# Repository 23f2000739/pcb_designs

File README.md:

# pcb_designs
* ⚙️ **[Buck Converter design](./buck_converter/)**
* ⚙️ **[Regulated Power Supply design](./power_supply/)**

 ## projects by--
 -Shreyasee Routray

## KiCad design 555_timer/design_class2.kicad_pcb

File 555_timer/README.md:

# LM555 Astable Multivibrator 

A free-running oscillator built around the LM555N timer, designed in KiCad.
It blinks an LED at about 1 Hz from a 9V supply.

## Overview
The LM555 is wired in astable mode. The timing capacitor charges through
R1 and R3 and discharges through R3 into the discharge pin, so the output
switches between HIGH and LOW on its own with no external trigger. The
output drives an LED through a current-limiting resistor.

## Circuit description
- **U1 (LM555N):** timer IC in astable mode
- **R1, R3, C2:** timing network
- **C1:** 0.01 µF decoupling capacitor on the control-voltage pin (pin 5)
- **R2 + D1:** LED output indicator with current-limiting resistor
- Pins 2 (TRIG) and 6 (THRES) are tied together and connected to C2
- Reset pin (4) is tied to Vcc, so the timer is always enabled

## Component values
| Ref | Value | Function |
|---|---|---|
| U1 | LM555N | Timer IC |
| R1 | 3.9 kΩ | Timing resistor |
| R3 | 68 kΩ | Timing resistor |
| C2 | 10 µF / 16 V (electrolytic) | Timing capacitor |
| C1 | 0.01 µF | Control-pin decoupling |
| R2 | 1 kΩ | LED current limiter |
| D1 | LED | Output indicator |

## Working principle
1. C2 charges through R1 and R3 toward Vcc.
2. At 2/3 Vcc the output goes LOW and C2 discharges through R3.
3. At 1/3 Vcc the output goes HIGH and C2 charges again.
4. This repeats continuously, so the LED blinks.

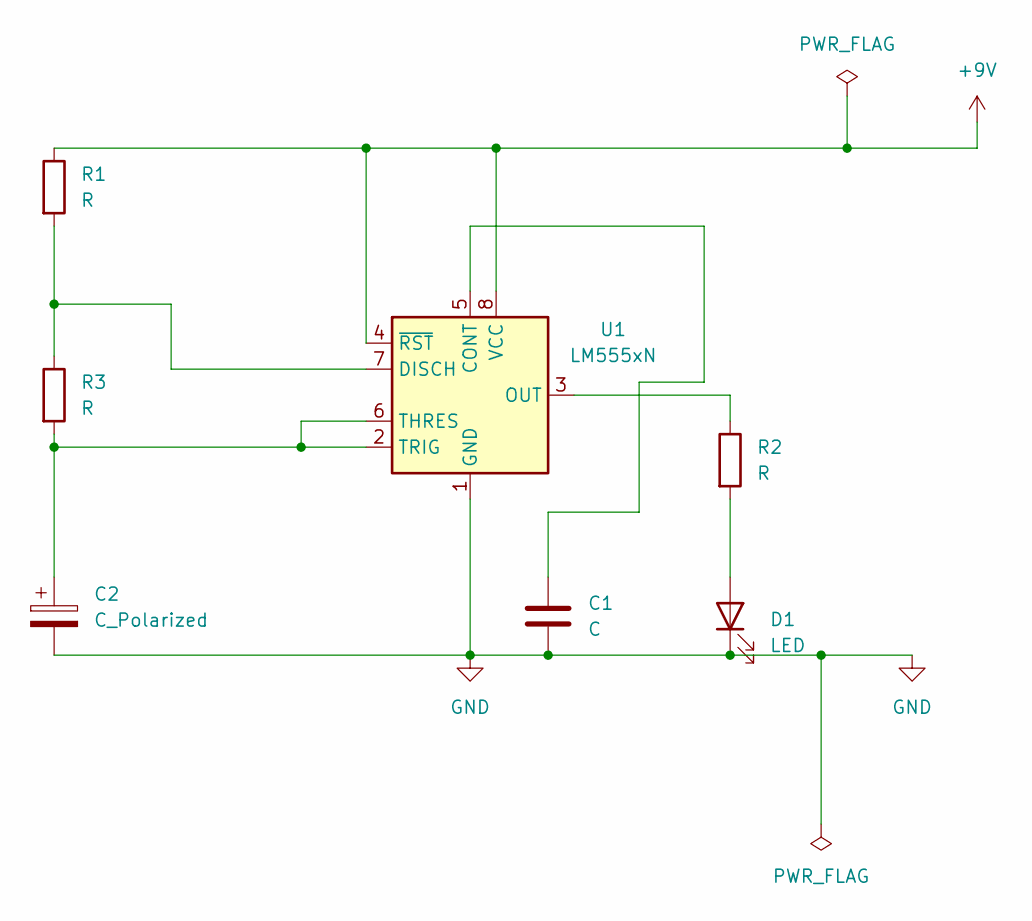
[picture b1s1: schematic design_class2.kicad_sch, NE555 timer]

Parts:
C1: C; C_Disc_D5.0mm_W2.5mm_P2.50mm
C2: C_Polarized; CP_Radial_D5.0mm_P2.00mm
D1: LED; LED_D5.0mm
R1, R2, R3: R; R_Axial_DIN0207_L6.3mm_D2.5mm_P7.62mm_Horizontal
U1: LM555xN; DIP-8_W7.62mm

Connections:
+9V: R1.1, U1.4 (~RST), U1.8 (VCC)
GND: C1.2, C2.2, D1.1 (K), U1.1 (GND)
unnamed: D1.2 (A), R2.2
unnamed: C1.1, U1.5 (CONT)
unnamed: R1.2, R3.1, U1.7 (DISCH)
unnamed: R2.1, U1.3 (OUT)
unnamed: C2.1, R3.2, U1.2 (TRIG), U1.6 (THRES)

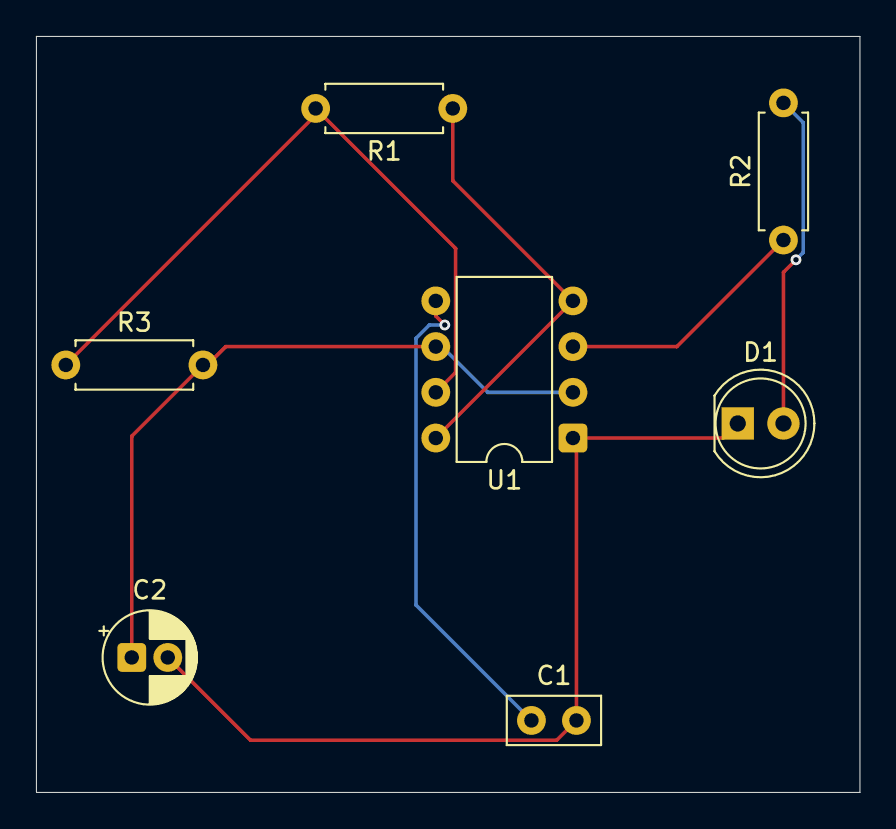
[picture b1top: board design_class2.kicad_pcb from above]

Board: 2 copper layers, 45.8 x 42.0 mm, 7 parts (0 on the bottom side), 7 nets.

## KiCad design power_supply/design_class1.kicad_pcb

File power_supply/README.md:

# 5V Regulated Power Supply (LM7805)

A linear regulated 5V DC power supply designed in KiCad. It converts an AC
transformer output into a stable 5V DC output using a bridge rectifier,
a reservoir capacitor and an LM7805 voltage regulator.

## Overview
The AC input is full-wave rectified by a bridge of four 1N4007 diodes and
smoothed by a filter capacitor. The LM7805 then regulates the DC voltage
down to a fixed 5V. A power LED shows when the output is live.

## Specifications
- Input: 9V-12V AC (from a step-down transformer)
- Output: 5V DC regulated
- Maximum output current: 1A (heatsink recommended at higher loads)
- Regulator: LM7805, TO-220 package

## Circuit description
- **J1:** AC input connector
- **D1-D4 (1N4007):** full-wave bridge rectifier
- **C1:** polarized filter (reservoir) capacitor
- **C2, C3:** high-frequency decoupling capacitors at the regulator input and output
- **U1 (LM7805):** 5V linear voltage regulator
- **R1 + D5:** power indicator LED with current-limiting resistor

## Working principle
1. The transformer steps the mains voltage down to a low AC voltage.
2. The bridge rectifier converts AC to pulsating DC.
3. C1 smooths the pulsating DC into DC with small ripple.
4. The LM7805 regulates this to a constant 5V.
5. C3 stabilizes the output, and the LED indicates power.

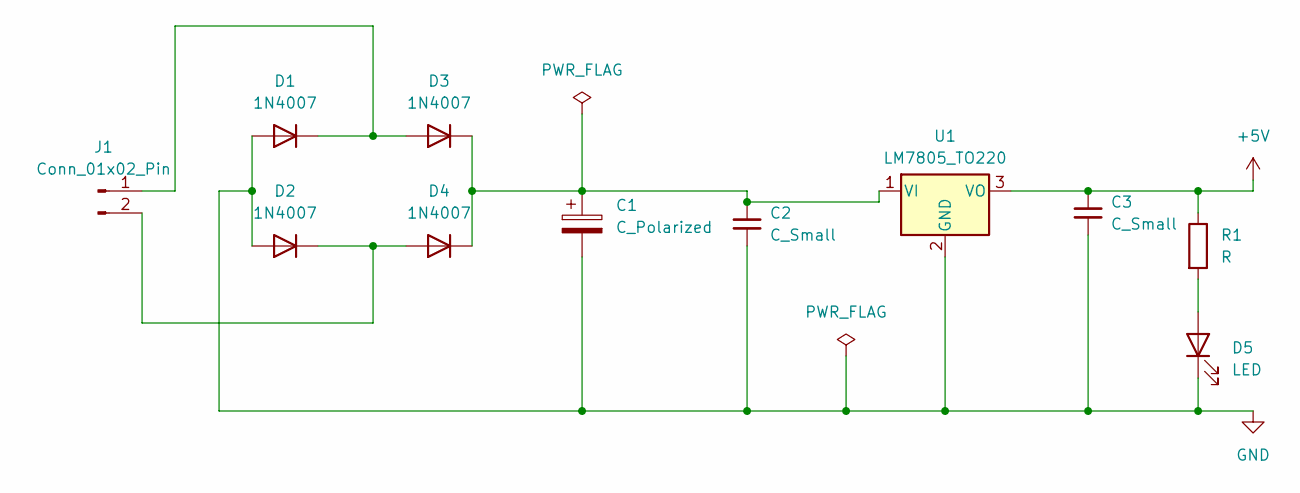
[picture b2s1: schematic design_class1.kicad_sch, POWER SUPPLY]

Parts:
C1: C_Polarized; C_0201_0603Metric
C2, C3: C_Small; C_0402_1005Metric_Pad0.74x0.62mm_HandSolder
D1, D2, D3, D4: 1N4007; D_DO-15_P10.16mm_Horizontal
D5: LED; LED_0201_0603Metric
J1: Conn_01x02_Pin; PinHeader_1x02_P1.00mm_Vertical
R1: R; R_0201_0603Metric
U1: LM7805_TO220; TO-220-3_Vertical

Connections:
+5V: C3.1, R1.1, U1.3 (VO)
GND: C1.2, C2.2, C3.2, D1.2 (A), D2.2 (A), D5.1 (K), U1.2 (GND)
unnamed: D1.1 (K), D3.2 (A), J1.1
unnamed: D2.1 (K), D4.2 (A), J1.2
unnamed: C1.1, C2.1, D3.1 (K), D4.1 (K), U1.1 (VI)
unnamed: D5.2 (A), R1.2

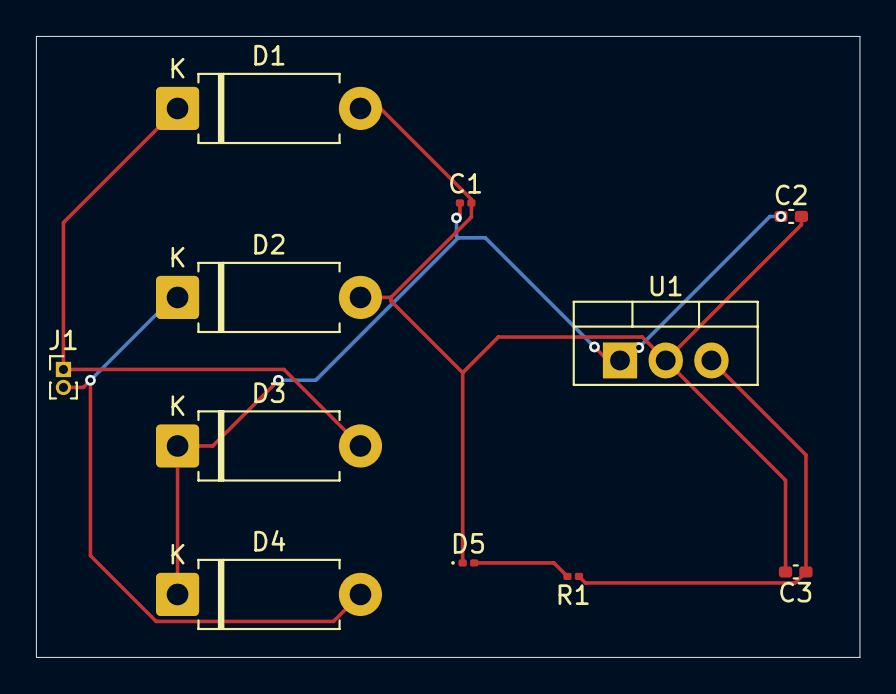
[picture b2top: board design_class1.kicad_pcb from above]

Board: 2 copper layers, 45.8 x 34.5 mm, 11 parts (0 on the bottom side), 6 nets.

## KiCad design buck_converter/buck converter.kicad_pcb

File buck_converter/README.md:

# LM2596 5V Buck Converter

A 5V fixed-output step-down (buck) DC-DC converter, designed in KiCad
(schematic capture and 2-layer PCB layout).

## Overview
The board steps a higher DC input voltage down to a regulated 5V using the
LM2596S-5 switching regulator (150 kHz, up to 3A). 

## Specifications
- Input voltage: 7V to 24V DC (limited by the 35V input capacitor rating)
- Output voltage: 5V fixed
- Maximum output current: up to 3A (with adequate heat dissipation)
- Switching frequency: 150 kHz (typical)
- Board: 2-layer PCB, through-hole connectors, SMD regulator/diode/inductor

- ## Circuit description
- **U1 – LM2596S-5:** integrated switch and control circuit; feedback pin
  connected directly to the 5V output (fixed-voltage version)
- **C1 – 100µF/35V:** input capacitor
- **L1:** energy-storage inductor
- **D2 – 1N5822:** Schottky catch diode
- **C2 – 330µF/10V:** output filter capacitor
- **D1 + R1 (330Ω):** power indicator LED
- **J1 / J2:** input and output connectors
- ON/OFF pin tied to GND, so the regulator is always enabled

- ## PCB design notes
- 1.2mm traces for input and output paths
- Catch diode and capacitors placed close to the regulator to keep the
  switching loop short.

- 

## 3d view

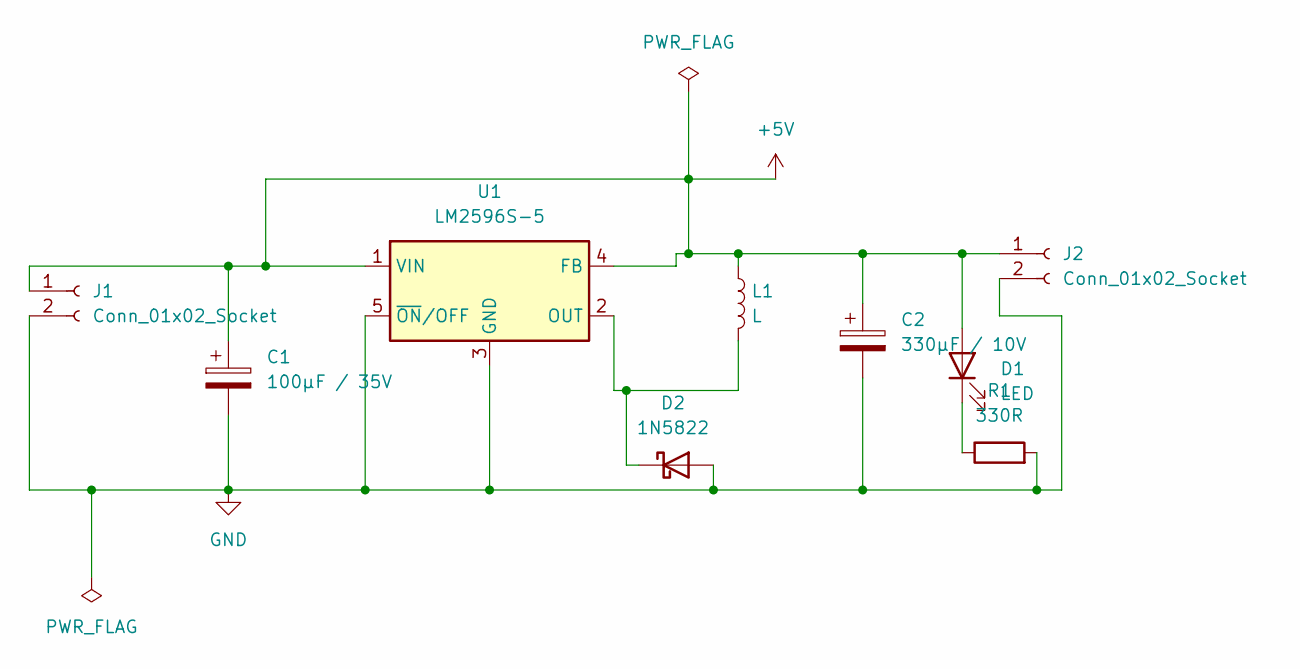
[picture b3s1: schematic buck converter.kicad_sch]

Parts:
C1: 100µF / 35V; CP_Radial_D6.3mm_P2.50mm
C2: 330µF / 10V; CP_Radial_D6.3mm_P2.50mm
D1: LED; LED_0805_2012Metric
D2: 1N5822; D_SMA
J1, J2: Conn_01x02_Socket; PinHeader_1x02_P2.54mm_Vertical
L1: L; L_7.3x7.3_H4.5
R1: 330R; R_0805_2012Metric
U1: LM2596S-5; TO-263-5_TabPin3

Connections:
+5V: C1.1, C2.1, D1.2 (A), J1.1, J2.1, L1.1, U1.1 (VIN), U1.4 (FB)
GND: C1.2, C2.2, D2.2 (A), J1.2, J2.2, R1.2, U1.3 (GND), U1.5 (~ON/OFF)
unnamed: D1.1 (K), R1.1
unnamed: D2.1 (K), L1.2, U1.2 (OUT)

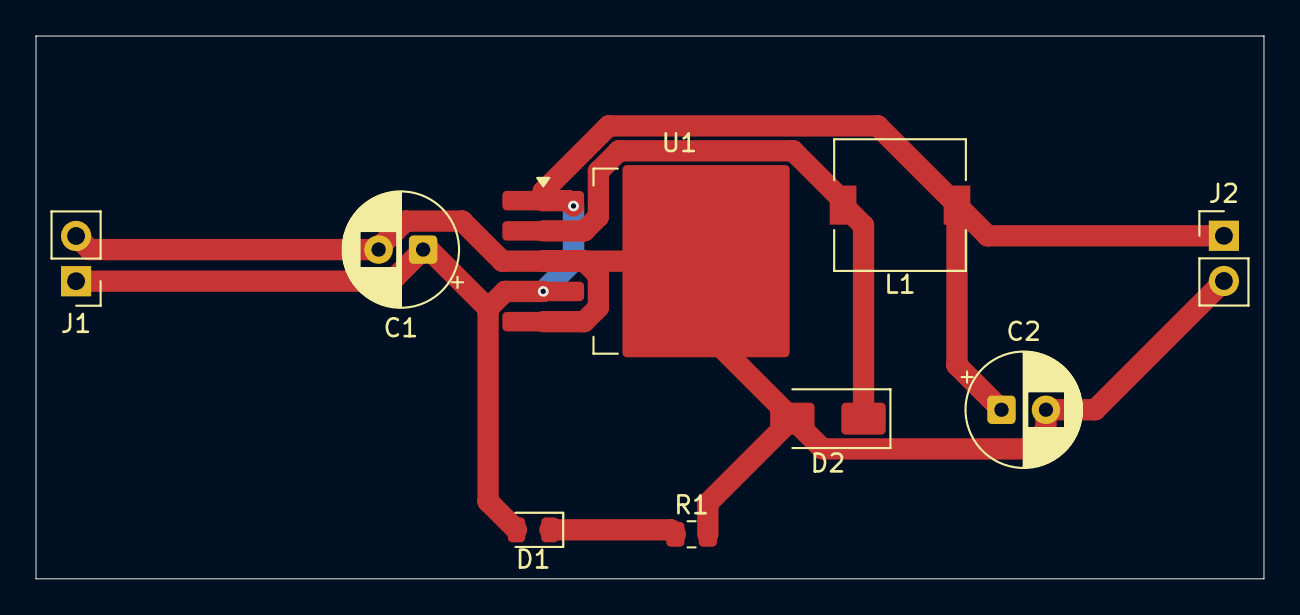
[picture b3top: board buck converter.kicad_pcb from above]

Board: 2 copper layers, 69.0 x 30.5 mm, 9 parts (0 on the bottom side), 4 nets.
